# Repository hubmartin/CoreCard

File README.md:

# CoreCard

microSD and 3.5mm audio extension board for **HARDWARIO Core Module NR**.

This board is soledered instead of SPIRIT1 radio module. It takes advantage of separate SPI bus so communication with SD card is not colliding with SPI bus on the Core Module pin headers. I've also added 3.5mm Jack connector on the bottom because there was nothing to place :) Now you can play WAV or MOD files and use PWM output with RC filter to play a mono music.

Take a look at the firmware repository for this project https://github.com/hubmartin/bcf-usb-sd-card

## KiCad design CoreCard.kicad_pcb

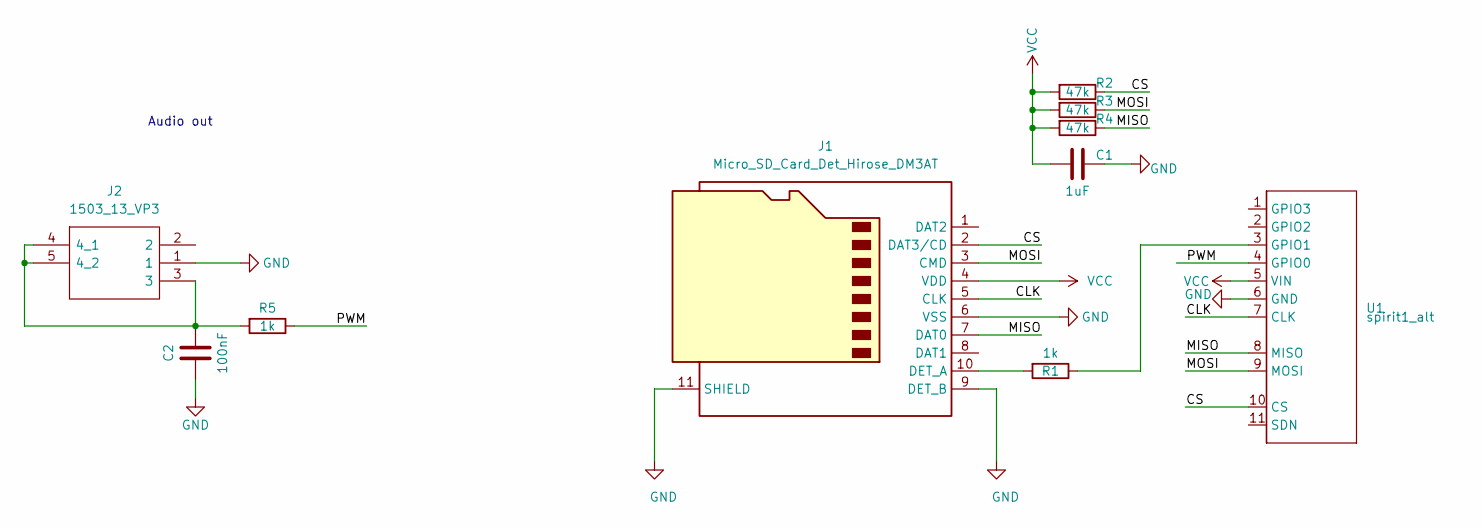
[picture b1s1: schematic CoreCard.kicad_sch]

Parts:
C1: 1uF; C_0603_1608Metric
C2: 100nF; C_0603_1608Metric
J1: Micro_SD_Card_Det_Hirose_DM3AT; microSD_HC_Hirose_DM3AT-SF-PEJM5
J2: 1503_13_VP3; 150313VP3; Manufacturer_Part_Number 1503 13 VP3
R1, R5: 1k; R_0603_1608Metric_Pad1.05x0.95mm_HandSolder
R2, R3, R4: 47k; R_0603_1608Metric_Pad1.05x0.95mm_HandSolder
U1: spirit1_alt

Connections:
/CLK: J1.5 (CLK), U1.7 (CLK)
/CS: J1.2 (DAT3/CD), R2.1, U1.10 (CS)
/MISO: J1.7 (DAT0), R4.1, U1.8 (MISO)
/MOSI: J1.3 (CMD), R3.1, U1.9 (MOSI)
/PWM: R5.1, U1.4 (GPIO0)
GND: C1.2, C2.1, J1.6 (VSS), J1.9 (DET_B), J1.11 (SHIELD), J2.1, U1.6 (GND)
unnamed: C2.2, J2.3, J2.4 (4_1), J2.5 (4_2), R5.2
unnamed: J1.10 (DET_A), R1.2
unnamed: R1.1, U1.3 (GPIO1)
VCC: C1.1, J1.4 (VDD), R2.2, R3.2, R4.2, U1.5 (VIN)

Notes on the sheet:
Audio out

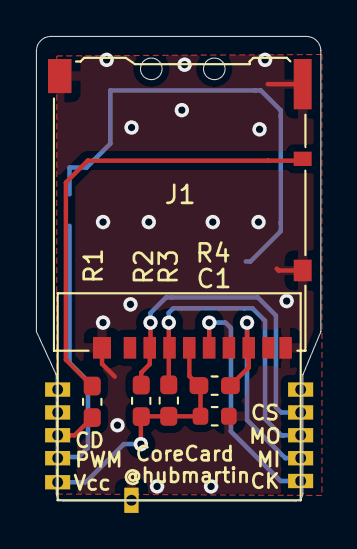
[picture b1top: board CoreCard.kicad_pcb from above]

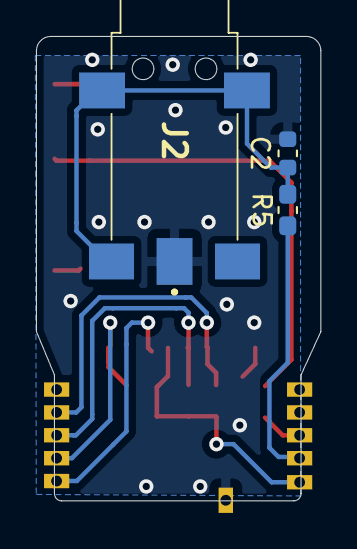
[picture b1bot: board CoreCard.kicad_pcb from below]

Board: 2 copper layers, 15.8 x 25.8 mm, 10 parts (3 on the bottom side), 10 nets.

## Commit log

2020-07-01 Add 3.5mm jack
2020-07-13 Init version
2020-07-13 Add readme & schematics PDF
